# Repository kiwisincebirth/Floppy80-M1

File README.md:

########################################################################

Floppy 80 for the TRS-80 Model I

The Floppy80-M1 emulates the following features of the Expansion Interface
- 32k RAM expansion
- Up to 3 floppy drives
  - 1 and 2 sided
  - single and double density
  - up to 90 cylinders
- Up to 2 hard drives

Configuration of the Floppy80-M1 is performed with the placement of
files on the SD-Card inserted in its card reader.
The files are as follows:

boot.cfg
- specified the default ini file to load at reset of the Floppy80
  when the floppy 80 boots or is reset it reads the contents of
  the boot.cfg to determine the default configuration ini file.

ini files
- specifies the disk images and options after reset.

  ini options
  - Drive0  - specified the image to load for drive :0
  - Drive1  - specified the image to load for drive :1
  - Drive2  - specified the image to load for drive :2
  - HD0     - specifies the image to load for tyhe first hard drive
  - HD1     - specifies the image to load for tyhe second hard drive
  - Doubler - 1 = doubler is enabled; 0 = doubler is disabled;
  - Mem     - 0 = disable upper memory; 1 = enable upper memory;
              if not specified upper memory is enabled by default.
  - Wait    - 0 = disable bus wait states; 1 = enable bus wait states.
              if not specified wait states are disable by default.

dmk files
- these are virtual disk images with a specific file format
  that allows them to be generated and used with a number
  of existing programs and simulators.

virtual hard drive images
- these are virtual hard drive images with a specific file format.
  They are used by the FreHD and TRS80-GP.

########################################################################

FDC utility
- Is a utility to interact with the Floppy80 from within the
  TRS-80 Model I operating environment.  Versions of FDC exist
  for the following operating systems

  - CPM 1.4.1 (Lifeboat)
  - CPM 1.5 (FMG)
  - Double DOS 4.2.4
  - DOS Plus 3.50
  - LDOS 5.3.1
  - MultiDOS 4.01
  - NEWDOS 3.0
  - NEWDOS 80 V2.0
  - TRSDOS 2.3
  - UltraDOS 4.2.0
  - VTDOS 3.0.0
  - VTDOS 4.0.1

  FDC.COM is used with the two CP/M OSs and
  FDC/CMD is used with the rest.

  Usage

  FDC OPT PARM1:drive

  Where:
  - OPT is one of the following
    - STA - returns the status of the Floppy80.
    - DIR - displays a list of file in the root folder of the SD-Card.
    - INI - switches between tyhe differnt ini file on the SD-Card.
    - DMK - allows the mounting of DMK disk images in the root folder
            of the SD-Card for a specified drive (0, 1 or 2).
    - FOR - copies a DMK disk image from the FOR folder of the SD-Card
            to one of the mounted disk images (0, 1 or 2).
    - IMP - imports a file from the root folder of the SD-Card
            into one of the mounted disk images (0, 1 or 2).

  FDC STA
  - Displays the contents to the ini file specified by boot.cfg

  FDC DIR filter
  - Displays a list of files in the root folder of the SD-Card.
    If filter is specified only files contain the filter character
    sequence are displayed.  If filter is not specified all files
    are displayed.

  FDC INI filename.exe
  - filename.exe is optional.  If not specified and list of ini files
    on the SD-Card will be displayed allow you to select the one to
    write to boot.cfg.  When specified FDC will bypass the file
    selection process.

  FDC DMK filename.exe n
  - filename.exe:n is optional.  When specified it will mount
    the dmk file names by filename.exe into the drive specified
    by n.  For example

    FDC DMK LDOS-DATA.DMK 2

    will mount the dmk file LDOS-DATA.DMK into drive :2

    If filename.exe:n is not specfied a list of dmk files
    will be listed allowing you to select on and the drive
    to mount it into.

  FDC FOR
  - list the files contained in the FMT folder of the SD-Card
    from which you can select one and specify the drive image
    to replace with it.  This is useful to generate blank disk
    images.

  FDC IMP filename.exe:n
  - imports the specified file from the root folder of the
    FAT32 formatted SD-Card to the disk image indicated by n.

########################################################################

Building Source
- Floppy80 firmware
  - Uses VSCode and the Pi Pico extension.

- FDC TRS (utility for the TRSDOS related utility)
  
  - zmac fdc.asm
  - use TRS80GP to import FDC/CMD onto a disk image
    
    - trs80gp -m1 -vs -frehd -frehd_dir zout -turbo -mem 48 -d0 dmk\ld531-0.dmk -d1 dmk\ld531-1.dmk -i "IMPORT2 FDC.CMD FDC/CMD:1\r"

- FDC CP/M (utility for the CP/M related utility)
  1. Compile program into a hex file.
  
       zmac fdc.asm
     
  2. Run TRS80GP loading the CP/M disk images.
     
       start trs80gp -m1 -vs -frehd -frehd_dir zout -turbo -mem 48 -d0 CPM141-0.dmk -d1 CPM141-1.dmk -d2 CPM141-2.dmk
     
  3. Select Load from TRS80GP File menu and select the hex file.
  
  4. Run "SAVE 20 B:FDC.COM" to save program memory contents to a .com file.
     As the program grows you will need to increase the value after SAVE.

     SAVE n ufn cr
     
       n   - number of 256-byte pages to be saved.
     
       ufn - unambiguous file name.
     
       cr  - carriage return.

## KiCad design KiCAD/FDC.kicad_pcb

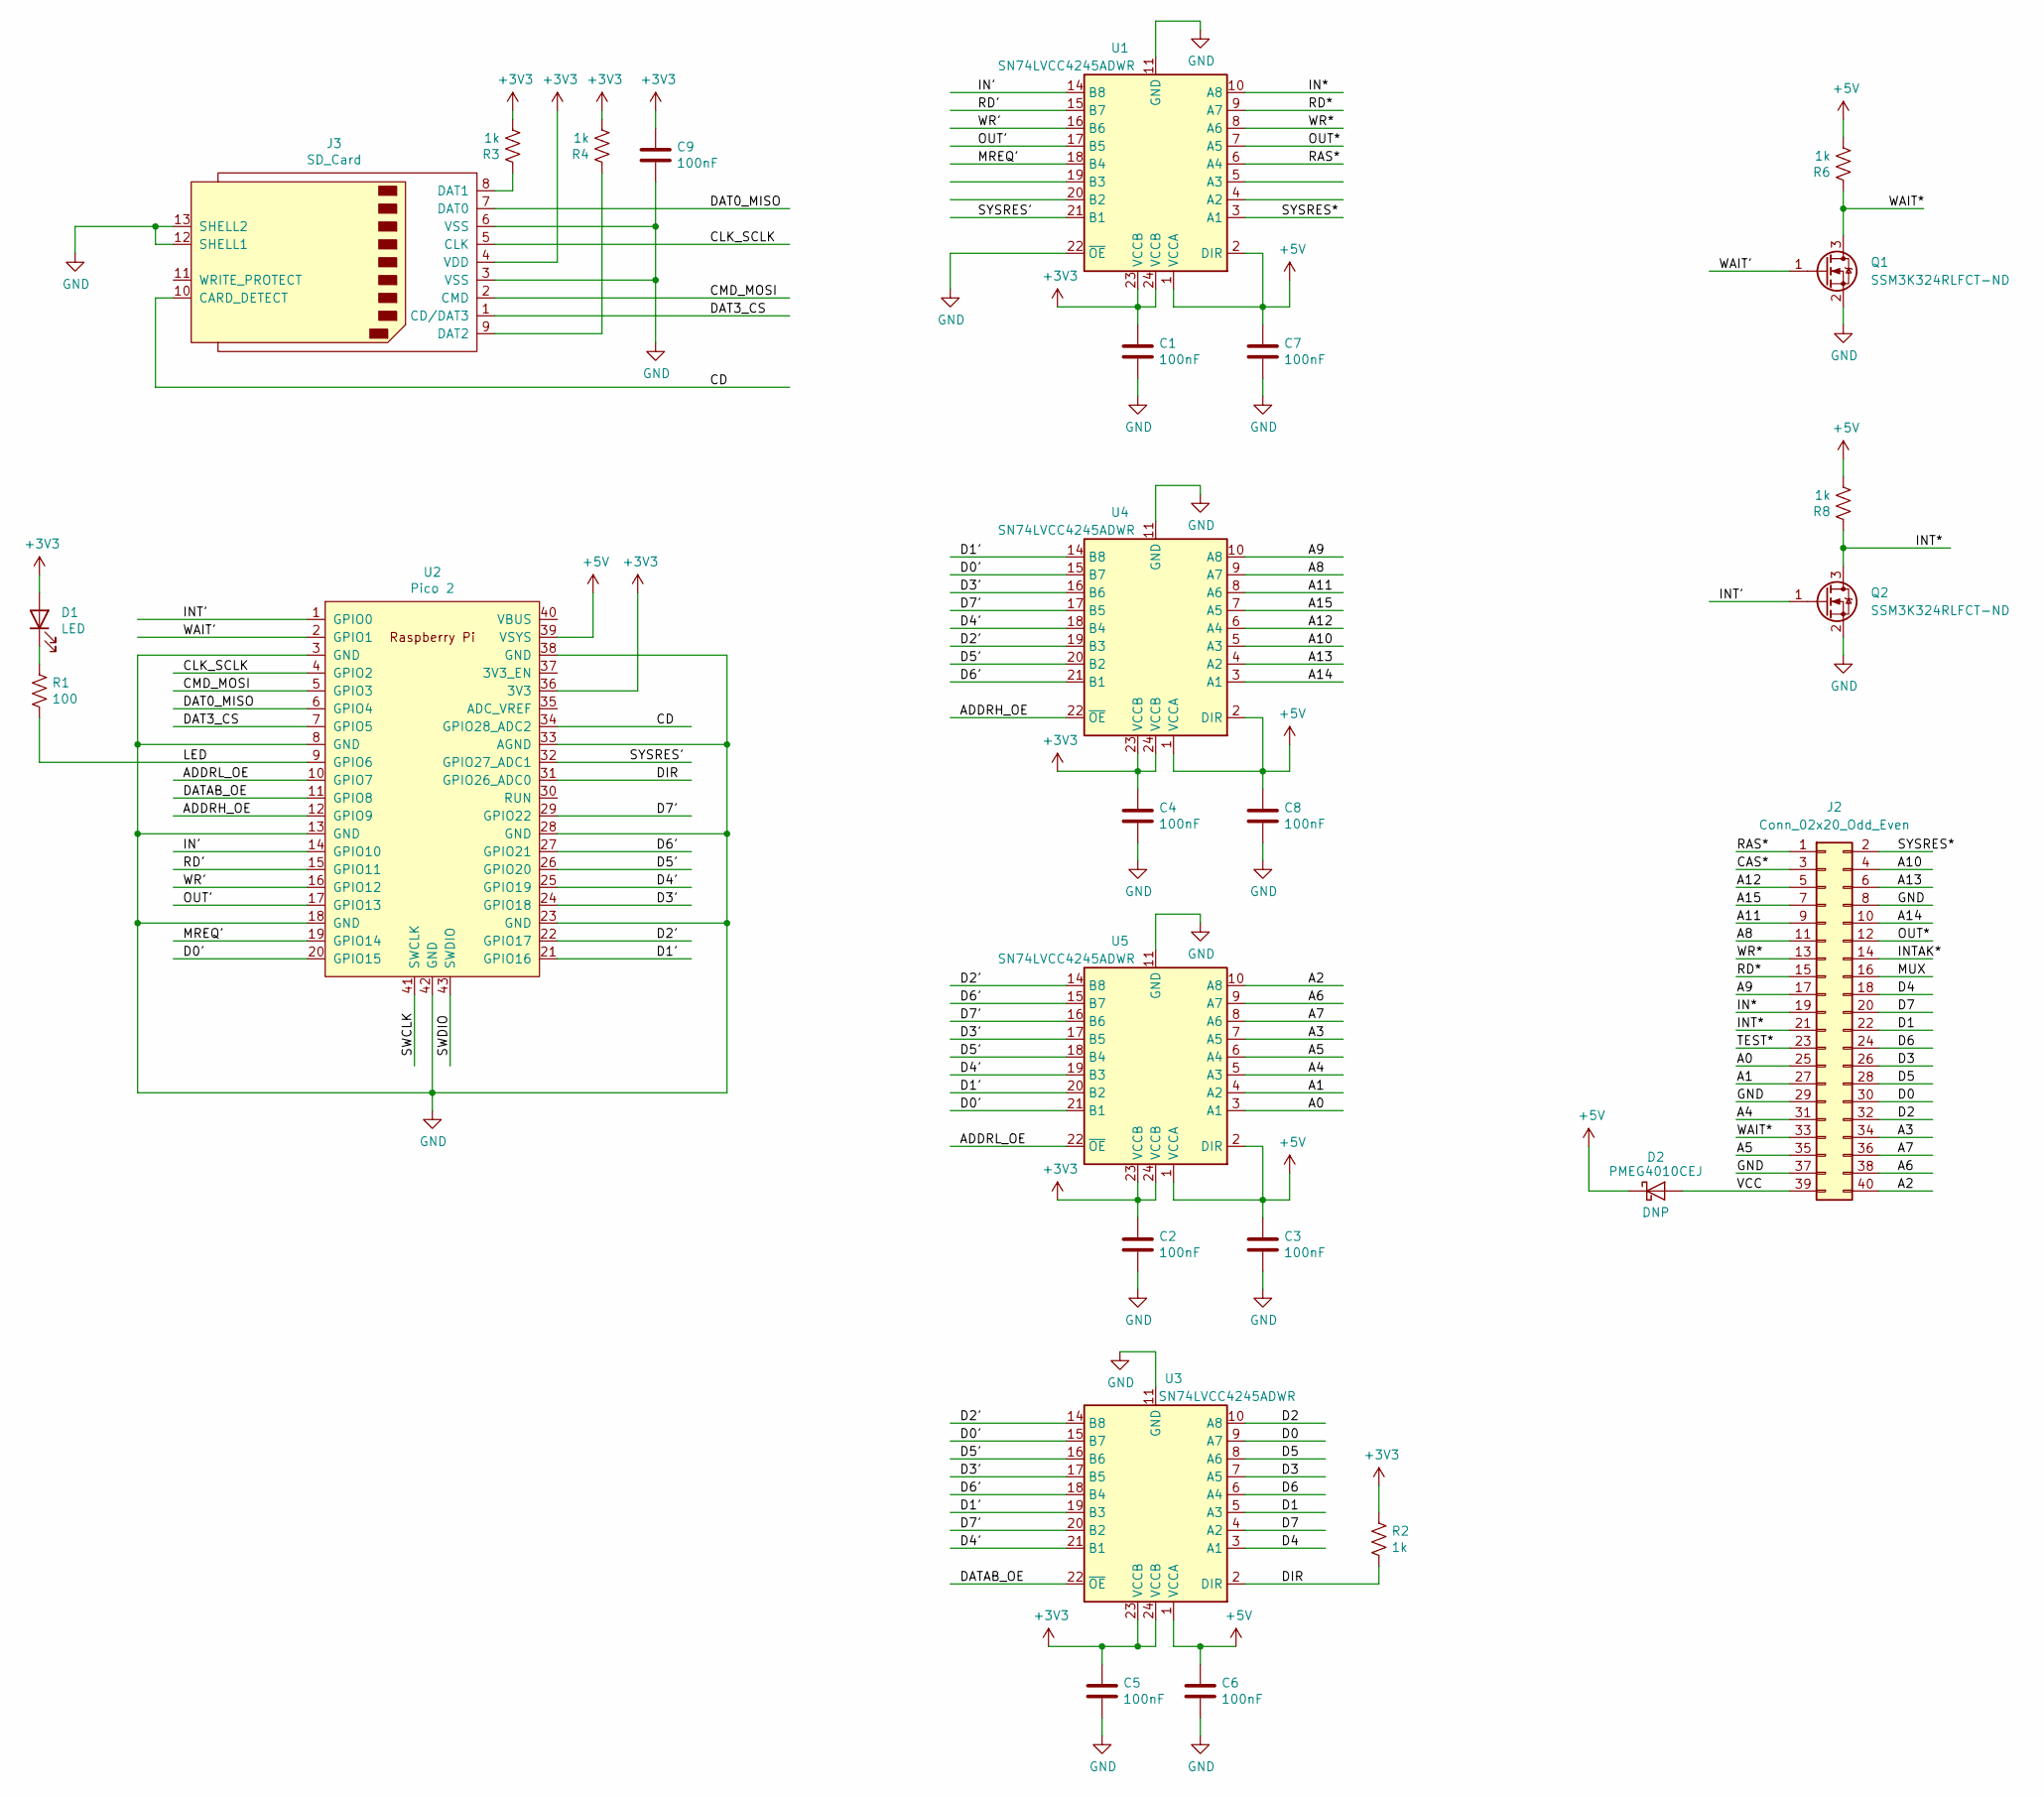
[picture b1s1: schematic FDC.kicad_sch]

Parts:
C1, C2, C3, C4, C5, C6, C7, C8, C9: 100nF; C_0805_2012Metric_Pad1.18x1.45mm_HandSolder; Digikey 732-8080-1-ND
D1: LED; LED_2816_7142Metric_Pad3.20x4.45mm_HandSolder; Digikey 754-1519-1-ND
D2: PMEG4010CEJ; D_SOD-323F
J2: Conn_02x20_Odd_Even; PinSocket_2x20_P2.54mm_Vertical; Part A31723-ND; Digikey A31723-ND
J3: SD_Card; SD_Kyocera_145638009511859+; Digikey 609-3956-1-ND
Q1, Q2: SSM3K324RLFCT-ND; SOT-23_Handsoldering; Digikey SSM3K324RLFCT-ND
R1: 100; R_0805_2012Metric_Pad1.20x1.40mm_HandSolder; Digikey RMCF0805FT100RCT-ND
R2, R3, R4, R6, R8: 1k; R_0805_2012Metric_Pad1.20x1.40mm_HandSolder; Digikey A106056CT-ND
U1, U3, U4, U5: SN74LVCC4245ADWR; SOIC-24W_7.5x15.4mm_P1.27mm; Digikey 296-26634-1-ND
U2: Pico 2; RPi_Pico_SMD_TH; Digikey 2648-SC1631CT-ND

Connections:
+3V3: C1.1, C2.1, C4.1, C5.1, C9.1, D1.2 (A), J3.4 (VDD), R2.1, R3.2, R4.2, U1.23 (VCCB), U1.24 (VCCB), U2.36 (3V3), U3.23 (VCCB), U3.24 (VCCB), U4.23 (VCCB), U4.24 (VCCB), U5.23 (VCCB), U5.24 (VCCB)
+5V: C3.1, C6.1, C7.1, C8.1, D2.1 (K), R6.2, R8.2, U1.1 (VCCA), U1.2 (DIR), U2.39 (VSYS), U3.1 (VCCA), U4.1 (VCCA), U4.2 (DIR), U5.1 (VCCA), U5.2 (DIR)
/A0: J2.25, U5.3 (A1)
/A1: J2.27, U5.4 (A2)
/A2: J2.40, U5.10 (A8)
/A3: J2.34, U5.7 (A5)
/A4: J2.31, U5.5 (A3)
/A5: J2.35, U5.6 (A4)
/A6: J2.38, U5.9 (A7)
/A7: J2.36, U5.8 (A6)
/A8: J2.11, U4.9 (A7)
/A9: J2.17, U4.10 (A8)
/A10: J2.4, U4.5 (A3)
/A11: J2.9, U4.8 (A6)
/A12: J2.5, U4.6 (A4)
/A13: J2.6, U4.4 (A2)
/A14: J2.10, U4.3 (A1)
/A15: J2.7, U4.7 (A5)
/ADDRH_OE: U2.12 (GPIO9), U4.22 (~OE)
/ADDRL_OE: U2.10 (GPIO7), U5.22 (~OE)
/CAS*: J2.3
/CD: J3.10 (CARD_DETECT), U2.34 (GPIO28_ADC2)
/CLK_SCLK: J3.5 (CLK), U2.4 (GPIO2)
/CMD_MOSI: J3.2 (CMD), U2.5 (GPIO3)
/D0: J2.30, U3.9 (A7)
/D0': U2.20 (GPIO15), U3.15 (B7), U4.15 (B7), U5.21 (B1)
/D1: J2.22, U3.5 (A3)
/D1': U2.21 (GPIO16), U3.19 (B3), U4.14 (B8), U5.20 (B2)
/D2: J2.32, U3.10 (A8)
/D2': U2.22 (GPIO17), U3.14 (B8), U4.19 (B3), U5.14 (B8)
/D3: J2.26, U3.7 (A5)
/D3': U2.24 (GPIO18), U3.17 (B5), U4.16 (B6), U5.17 (B5)
/D4: J2.18, U3.3 (A1)
/D4': U2.25 (GPIO19), U3.21 (B1), U4.18 (B4), U5.19 (B3)
/D5: J2.28, U3.8 (A6)
/D5': U2.26 (GPIO20), U3.16 (B6), U4.20 (B2), U5.18 (B4)
/D6: J2.24, U3.6 (A4)
/D6': U2.27 (GPIO21), U3.18 (B4), U4.21 (B1), U5.15 (B7)
/D7: J2.20, U3.4 (A2)
/D7': U2.29 (GPIO22), U3.20 (B2), U4.17 (B5), U5.16 (B6)
/DAT0_MISO: J3.7 (DAT0), U2.6 (GPIO4)
/DAT3_CS: J3.1 (CD/DAT3), U2.7 (GPIO5)
/DATAB_OE: U2.11 (GPIO8), U3.22 (~OE)
/DIR: R2.2, U2.31 (GPIO26_ADC0), U3.2 (DIR)
/IN': U1.14 (B8), U2.14 (GPIO10)
/IN*: J2.19, U1.10 (A8)
/INT': Q2.1 (G), U2.1 (GPIO0)
/INT*: J2.21, Q2.3 (D), R8.1
/INTAK*: J2.14
/LED: R1.2, U2.9 (GPIO6)
/MREQ': U1.18 (B4), U2.19 (GPIO14)
/MUX: J2.16
/OUT': U1.17 (B5), U2.17 (GPIO13)
/OUT*: J2.12, U1.7 (A5)
/RAS*: J2.1, U1.6 (A4)
/RD': U1.15 (B7), U2.15 (GPIO11)
/RD*: J2.15, U1.9 (A7)
/SWCLK: U2.41 (SWCLK)
/SWDIO: U2.43 (SWDIO)
/SYSRES': U1.21 (B1), U2.32 (GPIO27_ADC1)
/SYSRES*: J2.2, U1.3 (A1)
/TEST*: J2.23
/VCC: D2.2 (A), J2.39
/WAIT': Q1.1 (G), U2.2 (GPIO1)
/WAIT*: J2.33, Q1.3 (D), R6.1
/WR': U1.16 (B6), U2.16 (GPIO12)
/WR*: J2.13, U1.8 (A6)
GND: C1.2, C2.2, C3.2, C4.2, C5.2, C6.2, C7.2, C8.2, C9.2, J2.8, J2.29, J2.37, J3.3 (VSS), J3.6 (VSS), J3.12 (SHELL1), J3.13 (SHELL2), Q1.2 (S), Q2.2 (S), U1.11 (GND), U1.12 (GND), U1.13 (GND), U1.22 (~OE), U2.3 (GND), U2.8 (GND), U2.13 (GND), U2.18 (GND), U2.23 (GND), U2.28 (GND), U2.33 (AGND), U2.38 (GND), U2.42 (GND), U3.11 (GND), U3.12 (GND), U3.13 (GND), U4.11 (GND), U4.12 (GND), U4.13 (GND), U5.11 (GND), U5.12 (GND), U5.13 (GND)
unnamed: D1.1 (K), R1.1
unnamed: J3.8 (DAT1), R3.1
unnamed: J3.9 (DAT2), R4.1

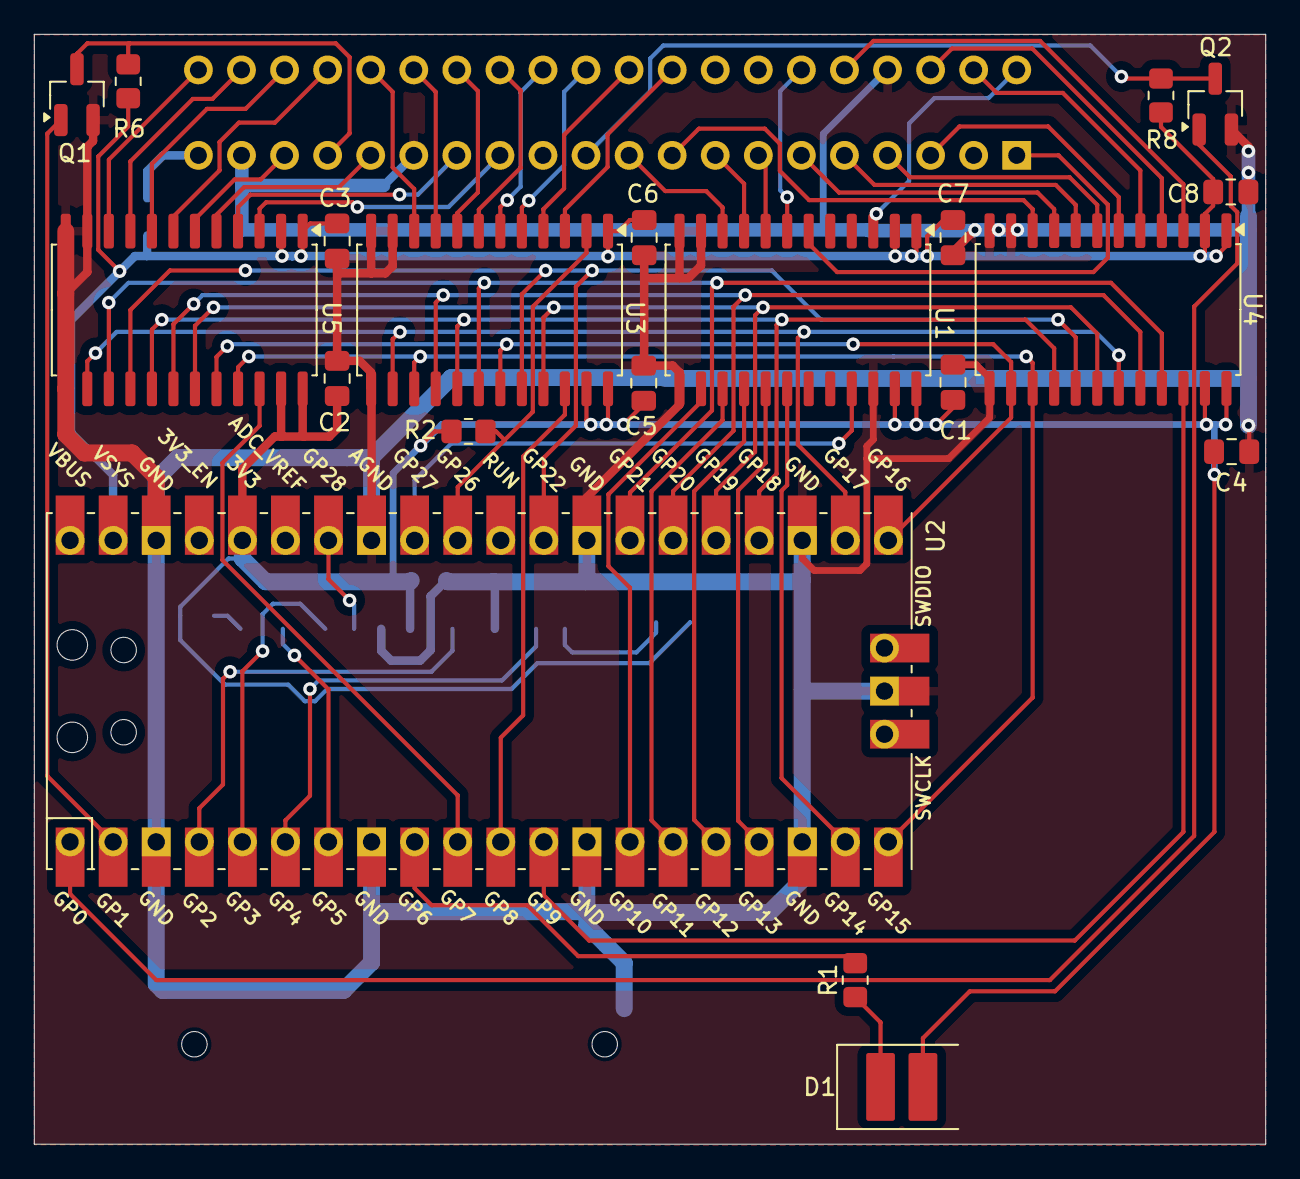
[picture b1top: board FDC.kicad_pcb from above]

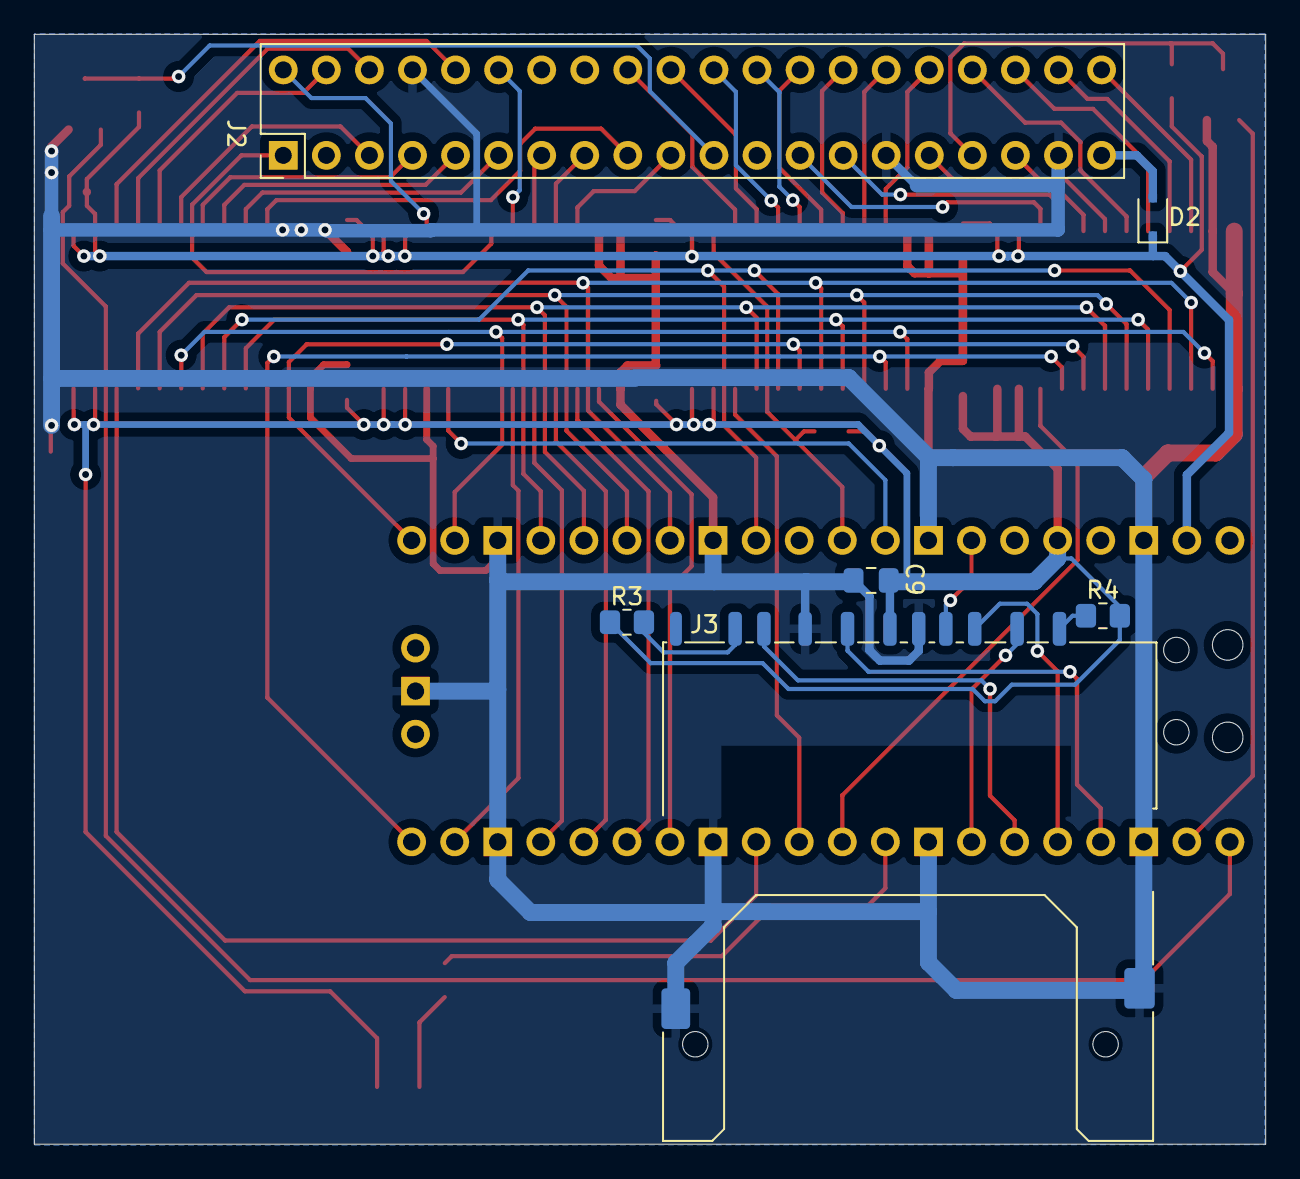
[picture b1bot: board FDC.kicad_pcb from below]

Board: 2 copper layers, 72.6 x 65.5 mm, 26 parts (6 on the bottom side), 65 nets.

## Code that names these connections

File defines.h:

#ifndef _H_DEFINES_
#define _H_DEFINES_

#define ENABLE_DOUBLER 1
#define ENABLE_LOGGING 1

//#pragma GCC optimize ("O0")
#pragma GCC optimize ("O3")

#include <stdio.h>

#define CDC_ITF     0           /* USB CDC interface no */

typedef signed char        	int8_t;
typedef unsigned char		uint8_t;
typedef short              	int16_t;
typedef unsigned short     	uint16_t;
typedef long               	int32_t;
typedef unsigned long      	uint32_t;
typedef long long          	int64_t;
typedef unsigned long long 	uint64_t;

typedef unsigned char		byte;
typedef unsigned short     	word;
typedef unsigned long      	dword;

#define SizeOfArray(x) (sizeof(x) / sizeof(x[0]))

// set to 1 to enable capture of bus activity logging to sd-card
#define ENABLE_TRACE_LOG 0

#define INT_PIN       0
#define WAIT_PIN      1
#define CLK_SCLK      2
#define CMD_MOSI      3

#define DAT0_MISO     4
#define DAT3_CS       5
#define LED_PIN       6
#define ADDRL_OE_PIN  7

#define DATAB_OE_PIN  8
#define ADDRH_OE_PIN  9
#define IN_PIN        10
#define RD_PIN        11

#define WR_PIN        12
#define OUT_PIN       13
#define MREQ_PIN      14
#define D0_PIN        15

#define D1_PIN        16
#define D2_PIN        17
#define D3_PIN        18
#define D4_PIN        19

#define D5_PIN        20
#define D6_PIN        21
#define D7_PIN        22

#define DIR_PIN       26
#define SYSRES_PIN    27
#define CD_PIN        28

// Bit  Net      Input    Hex
//             (1=input)
// 31    -         0
// 30    -         0
// 29    -         0
// 28    CD        1       1     0
//
// 27    SYSRES    1
// 26    DIR       0
// 25    -         0
// 24    -         0       8     0
//
// 23    -         0
// 22    D7        1
// 21    D6        1
// 20    D5        1       7     7
//
// 19    D4        1
// 18    D3        1
// 17    D2        1
// 16    D1        1       F     F
//
// 15    D0        1
// 14    RAS       1
// 13    OUT       1
// 12    WR        1       F     8
//
// 11    RD        1
// 10    IN        1
//  9    ADDRH     0
//  8    DATAB     0       C     0
//
//  7    ADDRL     0
//  6    LED       0
//  5    DAT3_CS   0
//  4    DAT0_MISO 0       0     0
//
//  3    CMD_MOSI  0
//  2    CLK_SCLK  0
//  1    WAIT      0
//  0    INT       0       0     0

#define GPIO_IN_MASK  0x187FFC00
#define DATA_BUS_MASK 0x007F8000

#define A_TO_B_DIR 1
#define B_TO_A_DIR 0

///////////////////////////////////////////////////////////////////////////////////////////////////

#define get_gpio_data_byte() (sio_hw->gpio_in >> D0_PIN)
#define get_gpio_read_bus()  (sio_hw->gpio_in >> IN_PIN)
#define get_gpio(gpio)       (sio_hw->gpio_in & (1u << gpio))
#define set_gpio(gpio)        sio_hw->gpio_set = 1u << gpio
#define clr_gpio(gpio)        sio_hw->gpio_clr = 1u << gpio
#define set_bus_as_output()   sio_hw->gpio_oe_set = 0xFF << D0_PIN
#define set_bus_as_input()    sio_hw->gpio_oe_clr = 0xFF << D0_PIN
#define put_byte_on_bus(data) sio_hw->gpio_togl = (sio_hw->gpio_out ^ (data << D0_PIN)) & (0xFF << D0_PIN)

// #define get_gpio_data_byte()  gpio_get_all() >> D0_PIN
// #define get_gpio(gpio)        gpio_get(gpio)
// #define set_gpio(gpio)        gpio_put(gpio, 1)
// #define clr_gpio(gpio)        gpio_put(gpio, 0)
// #define set_bus_as_output()   gpio_set_dir_out_masked(0xFF << D0_PIN)
// #define set_bus_as_input()    gpio_set_dir_in_masked(0xFF << D0_PIN)
// #define put_byte_on_bus(data) gpio_put_masked(0xFF << D0_PIN, data << D0_PIN)

///////////////////////////////////////////////////////////////////////////////////////////////////

// Low Power Timer Overflow Rates in Hz
#define TIMER_OVERFLOW_RATE 2000

///////////////////////////////////////////////////////////////////////////////////////////////////
// generic defines/equates

#ifndef TRUE
	#define FALSE	0
	#define TRUE	1
#endif

#ifndef true
	#define false	0
	#define true	1
#endif

#ifndef MAX_PATH
  #define MAX_PATH 64
#endif

///////////////////////////////////////////////////////////////////////////////////////////////////
// FDC logging

typedef struct {
	uint8_t type;
	uint8_t val;
	uint8_t op1;
	uint8_t op2;
} LogType;

#define LOG_SIZE 4096

extern LogType fdc_log[LOG_SIZE];
extern int log_head;
extern int log_tail;

enum {
	write_drive_select = 0,
	write_data,
	write_sector,
	write_track,
	write_cmd,
	read_drive_select,
	read_data,
	read_sector,
	read_track,
	read_status,
	port_out,
	port_in
};

///////////////////////////////////////////////////////////////////////////////////////////////////
// typedefs

typedef struct {
   uint64_t nSectorsTotal;
   uint64_t nSectorsFree;
   uint64_t nSectorSize;

   uint32_t nClustersTotal;
   uint32_t nClustersFree;
   uint32_t nClustersUsed;
   uint32_t nClustersBad;
   uint32_t nClusterSize;
} F_SPACE;

///////////////////////////////////////////////////////////////////////////////////////////////////
// enumerations

enum {
  opRead = 0,
  opWrite,
  opNop
};

///////////////////////////////////////////////////////////////////////////////////////////////////
// global variables

//-----------------------------------------------------------------------------
// counter for real time clock (RTC).

extern volatile uint8_t sd_byCardInialized;
extern volatile byte    g_byFdcIntrActive;
extern volatile byte    g_byRtcIntrActive;
extern volatile byte    g_byResetActive;
extern volatile byte    g_byEnableIntr;
extern volatile int32_t g_nRotationCount;

///////////////////////////////////////////////////////////////////////////////////////////////////

void InitVars(void);
void ReleaseWait(void);

byte* TD230_GetPtr(void);
int   TD230_Size(void);

///////////////////////////////////////////////////////////////////////////////////////////////////

#endif

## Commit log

2024-10-11 Cleanup
2024-10-12 First successful formatting of drive.
2024-10-13 Removed cpm type drives.
2024-10-13 Reduced SPI clock to 5MHz for more reliability.
2024-10-13 Improves performance of video to VT100 output.
2024-10-15 Implements mount request/response
2024-10-15 Saves and restores modified registers.
2024-10-22 Waked back changes for portability with no loss in performance.
2024-10-22 More of the same.
2024-10-22 Improves portability.
2024-10-23 Changes to allow for fast and slow memory operations. Slow memory operations add wait states. Fast do not. Previously all accesses imposed wait states.
2024-10-25 Index status is simulated as 1.8 degrees of rotation.
2024-10-25 Switched to pico 2
2024-10-26 Define for nop delay
2024-10-26 Cleanup and speed boost.
2024-10-26 Moved memory access code to a new source file. Start of restructuring for speed.
2024-10-26 Correct to hang and display reset message when specifying the INI file for boot.
2024-10-26 Adds support for non-IBM 16-byte sectors, which adda support for VTDOS 3.0.0
2024-10-26 Reduced drive strength on GPIO outputs.
2024-10-27 Boots all listed OSes
2024-10-27 Supports easier switch from pico to pico 2.
2024-11-01 Corrects CRC write to disk error. Allows formatting of drives under CP/M.
2024-11-01 Enables wait states for a RP2040
2024-11-02 Included the CP/M version of FDC.
2024-11-03 Activates WAIT for all memory operations. Sacrifices speed for stability.
2024-11-03 Adding hardware design to the repository.
2024-11-03 Changes for stability, don't know why they make it more stable yet.
2024-11-05 Code review.
2024-11-06 Stability over speed.
2024-11-06 Recovery from card removal.
2024-11-12 Fully decodes FDC commands.
2024-11-12 Regresion
2024-11-13 Performance improvements.
2024-11-14 Increased speed. No wait states imposed.
2024-11-15 Verifies s drive number was specified.
2024-11-15 Read high byte of address while waiting for MREQ. Allows code to respond faster when MREQ goes active (low).
2024-11-15 Copy command verified to work with latest firmware.
2024-11-21 Adds support for the Radio Shack Double Density Adapter.
2024-11-23 Version 0.1.0
2024-12-22 Modified to be compatible with M1-Floppy80
2024-12-22 Removed CLI
2024-12-22 Removes unused filers.
2024-12-22 Replaces disassembled instructions as data statements.
2024-12-22 More the same.
2024-12-25 More cleanup of the disassembled code.
2025-09-22 Resets system after reset line is low for > 1ms
2025-09-24 Switches to the watchdog for a system reset
2025-09-24 Uses the new reset function.
2025-09-24 Removes double density checks from WD1771 since it does not support double density.
2025-09-27 Enable CLI while waiting for release of reset line.
2025-09-27 Arranged OSs in order they are listed by FDC INI
2025-09-27 Corrects an error is setting the DRQ status bit
2025-09-27 Added to follow datasheet more closely.
2025-09-27 Adds support for both E=0 and E=1
2025-09-27 File should not have been added to repository
2025-09-29 Added command to format a drive on Double DOS
2025-09-30 Tracks drive select, command code and command type.
2025-09-30 Corrections.
2025-10-03 Checks available space for TX CDC buffer before writing to the CDC.
2025-10-07 Improvements to the cli
2025-10-16 Corrected issue were INTR output needs to be disabled after RD line goes inactive.
2025-10-18 First working virtual hard disk
2025-10-19 Virtual hard drive now uses the FreHD file format.
2025-10-20 Improves timing to resolve backup/cmd issue while still supporting HDC emulation.
2025-10-22 Adds ini entry to enable doubler
2025-11-27 Moved firmware source to its own folder
2025-12-04 User Guide
2025-12-07 improved docs
2025-12-07 Replaced old readme with new.
2025-12-09 Filtering of hidden files
2025-12-17 Updates schematic part numbers
